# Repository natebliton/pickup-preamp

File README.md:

# pickup-preamp
KiCAD project for violin/viola piezo project

I primarily use a Kremona pickup for my viola, and initially designed a preamp to work with that.

I also have a backup instrument that instead has a fishman pickup that requires a "high impedance preamp". So, the next step is to either make another preamp that works for that, or to modify the initial design in order to have adjustable input impedance (hopefully the latter).

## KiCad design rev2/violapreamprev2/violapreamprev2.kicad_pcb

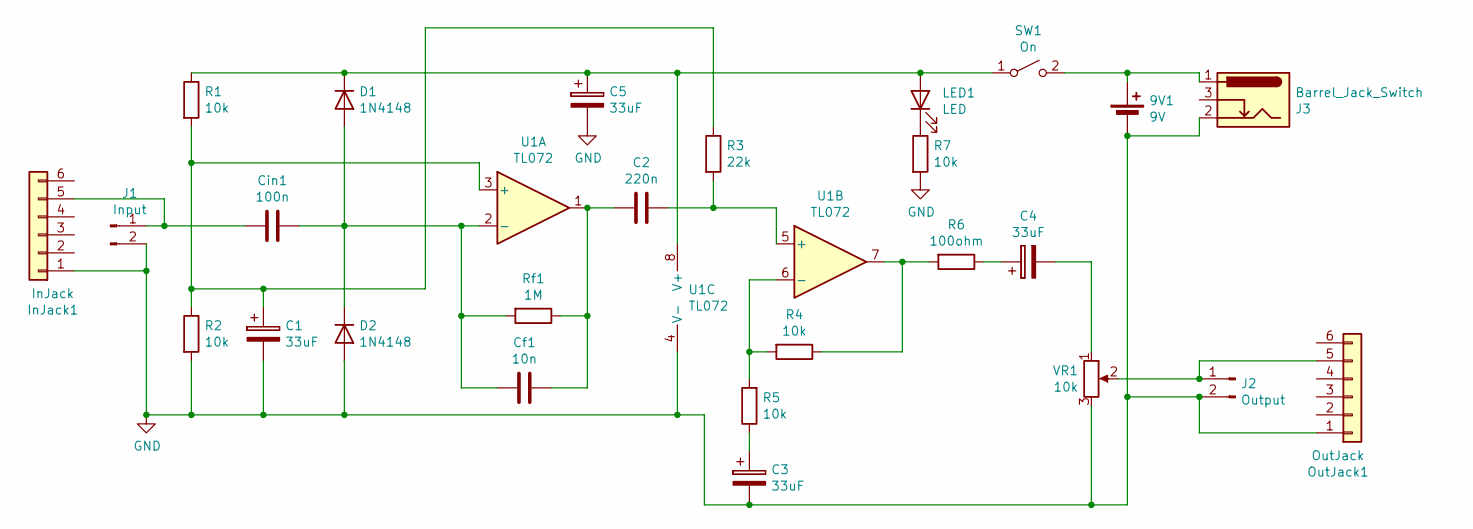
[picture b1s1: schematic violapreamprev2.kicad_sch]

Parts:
9V1: 9V; PinHeader_1x02_P2.54mm_Vertical
C1, C3, C4, C5: 33uF; CP_Radial_D6.3mm_P2.50mm
C2: 220n; C_Disc_D7.5mm_W2.5mm_P5.00mm
Cf1: 10n; C_Disc_D7.5mm_W2.5mm_P5.00mm
Cin1: 100n; C_Disc_D7.5mm_W2.5mm_P5.00mm
D1, D2: 1N4148; D_DO-35_SOD27_P7.62mm_Horizontal
InJack1: InJack; StereoJackTRS3
J1: Input; PinHeader_1x02_P2.54mm_Vertical
J2: Output; PinHeader_1x02_P2.54mm_Vertical
J3: Barrel_Jack_Switch; BarrelJack_Horizontal
LED1: LED; LED_D5.0mm
OutJack1: OutJack; StereoJackTRS3
R1, R2, R4, R5, R7: 10k; R_Axial_DIN0207_L6.3mm_D2.5mm_P7.62mm_Horizontal
R3: 22k; R_Axial_DIN0207_L6.3mm_D2.5mm_P7.62mm_Horizontal
R6: 100ohm; R_Axial_DIN0207_L6.3mm_D2.5mm_P7.62mm_Horizontal
Rf1: 1M; R_Axial_DIN0207_L6.3mm_D2.5mm_P7.62mm_Horizontal
SW1: On; PinHeader_1x02_P2.54mm_Vertical
U1: TL072; DIP-8_W7.62mm_Socket_LongPads
VR1: 10k; PinHeader_1x03_P2.54mm_Vertical

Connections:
GND: 9V1.2 (-), C1.2, C3.2, C5.2, D2.2 (A), InJack1.1, J1.2, J2.2, J3.2, OutJack1.1, R2.2, R7.2, U1.4 (V-), VR1.3
unnamed: 9V1.1 (+), J3.1, SW1.2 (B)
unnamed: C1.1, R1.2, R2.1, R3.1, U1.3 (+)
unnamed: C2.1, R3.2, U1.5 (+)
unnamed: C2.2, Cf1.1, Rf1.1, U1.1
unnamed: C3.1, R5.1
unnamed: C4.1, R6.1
unnamed: C4.2, VR1.1
unnamed: C5.1, D1.1 (K), LED1.2 (A), R1.1, SW1.1 (A), U1.8 (V+)
unnamed: Cf1.2, Cin1.1, D1.2 (A), D2.1 (K), Rf1.2, U1.2 (-)
unnamed: Cin1.2, InJack1.5, J1.1
unnamed: J2.1, OutJack1.5, VR1.2
unnamed: LED1.1 (K), R7.1
unnamed: R4.1, R6.2, U1.7
unnamed: R4.2, R5.2, U1.6 (-)

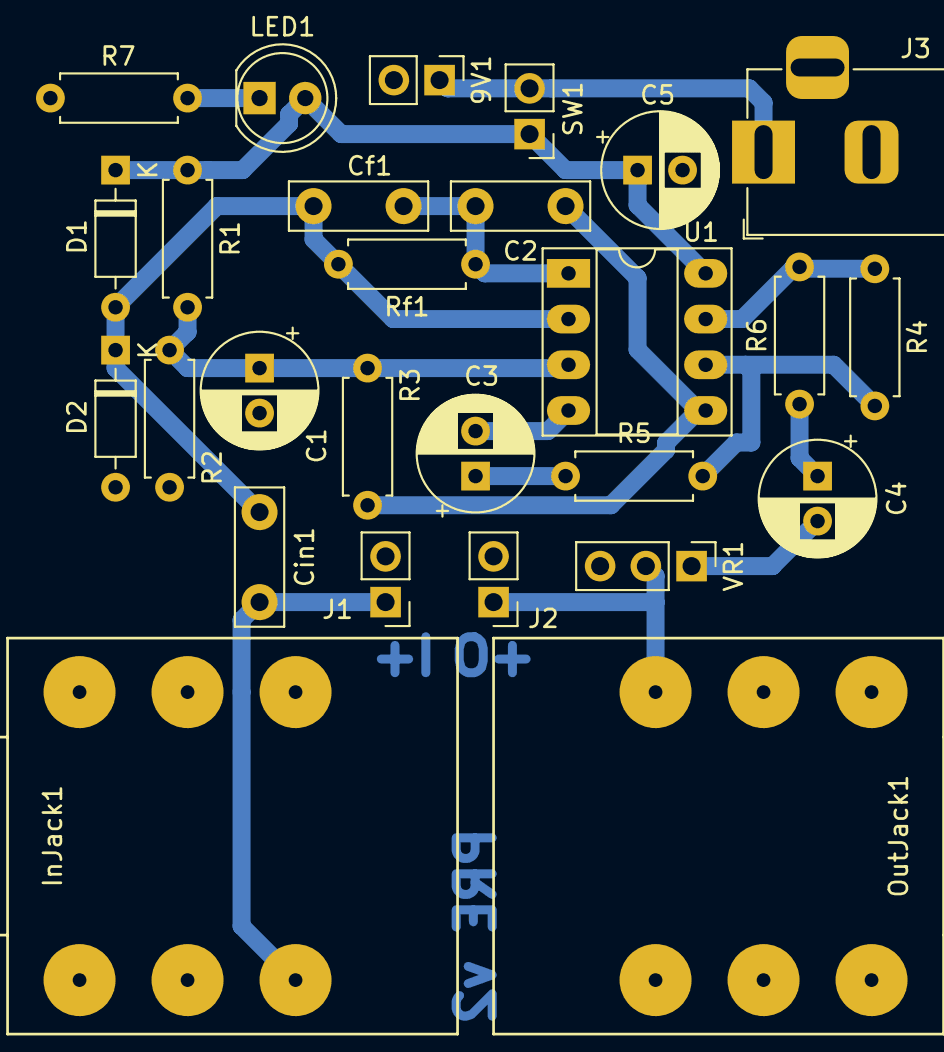
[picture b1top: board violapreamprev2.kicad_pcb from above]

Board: 2 copper layers, 27 parts (0 on the bottom side), 15 nets.

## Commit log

2020-09-28 starting kicad project
2020-09-28 laying it all out
2020-11-24 added ground plane, bits of labeling
2020-11-25 added power jack
2020-11-25 add jacks, remap for v2
2020-11-25 added print files
2024-09-08 adding branch from original design and starting transistor version too
